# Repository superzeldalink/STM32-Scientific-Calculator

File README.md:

# STM32 Scientific Calculator

## Features
- [x] Basic calculation with
  - [x] $+$, $-$, $\times$, $\div$
  - [x] $\sqrt x$, $\sqrt[a]x$, $a^b$
  - [x] $\sin x$, $\cos x$, $\tan x$ 
  - [ ] $\arcsin x$, $\arccos x$, $\arctan x$ 
  - [ ] $\sinh x$, $\cosh x$, $\tanh x$ 
  - [x] $\ln x$, $\log_{10}x$, $\log_a x$
  - [x] Factorial $!$
- [x] Limits
- [x] Differentiation
- [x] Integration
- [x] Solve equation
- [x] CALC and STO (3 variables for now)
- [x] Convert decimal places into fractions
- [x] Accuracy upto 10 decimal places
- [x] Cursor to move left and right
- [x] Graph function

## Documents
- Schematic: [pcb_schematic.pdf](Report/PCB/pcb_schematic.pdf)
- PCB: [pcb.pdf](Report/PCB/pcb.pdf)
- Project Report: [Report.pdf](Report.pdf)

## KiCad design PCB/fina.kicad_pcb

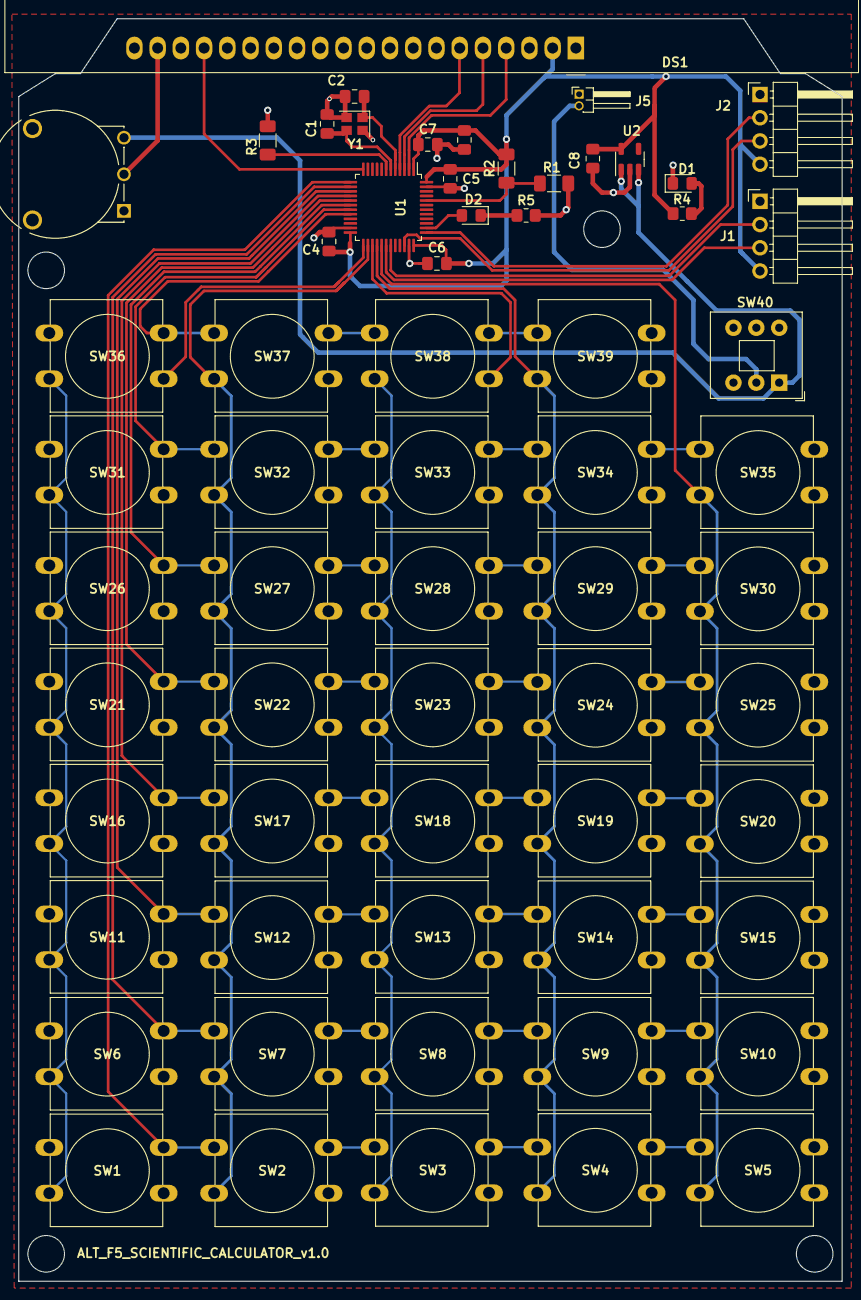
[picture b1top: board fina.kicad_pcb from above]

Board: 2 copper layers, 90.0 x 138.0 mm, 63 parts (0 on the bottom side), 33 nets.

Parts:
C1, C2: 20pF; C_0805_2012Metric_Pad1.18x1.45mm_HandSolder
C3: 4uF; C_0805_2012Metric_Pad1.18x1.45mm_HandSolder
C4, C5, C6, C7: 100pF; C_0805_2012Metric_Pad1.18x1.45mm_HandSolder
C8: 1uF; C_0805_2012Metric_Pad1.18x1.45mm_HandSolder
D1: PWR_LED; LED_0805_2012Metric_Pad1.15x1.40mm_HandSolder
D2: STATUS_LED; LED_0805_2012Metric_Pad1.15x1.40mm_HandSolder
DS1: ST7920; ST7920_128x64
J1: UART; PinHeader_1x04_P2.54mm_Horizontal
J2: SWD; PinHeader_1x04_P2.54mm_Horizontal
J5: PWR; PinHeader_1x02_P1.27mm_Horizontal
R1: 10K; R_1206_3216Metric_Pad1.30x1.75mm_HandSolder
R2, R3: 0; R_1206_3216Metric_Pad1.30x1.75mm_HandSolder
R4, R5: 330; R_0805_2012Metric_Pad1.20x1.40mm_HandSolder
R6: RV100F-30-4K1B-B10K-B301; TRIM_RV100F-30-4K1B-B10K-B301
SW1, SW2, SW3, SW4, SW5, SW6, SW7, SW8, SW9, SW10, SW11, SW12, SW13, SW14, SW15, SW16, SW17, SW18, SW19, SW20, SW21, SW22, SW23, SW24, SW25, SW26, SW27, SW28, SW29, SW30, SW31, SW32, SW33, SW34, SW35, SW36, SW37, SW38, SW39: SW_Push; SW_PUSH-12mm
SW40: SW_SPDT; SW_Push_2P2T_Toggle_CK_PVA2OAH5xxxxxxV2
U1: STM32F302CCTx; LQFP-48_7x7mm_P0.5mm
U2: SPX3819M5-L-3-3; SOT-23-5
Y1: 32MHz; Crystal_SMD_2520-4Pin_2.5x2.0mm

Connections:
3.3V: C3.1, C4.1, C5.1, C6.1, C7.1, C8.1, DS1.2 (VCC), J1.4, J2.4, R2.1, R4.1, U1.1 (VBAT), U1.24 (VDD), U1.36 (VDD), U1.48 (VDD), U2.5 (OUT)
4.2V: R6.3, SW40.1 (A), U2.1 (IN), U2.3 (EN)
/BATT: J5.2, SW40.2 (B)
E: DS1.6 (E), U1.4 (PC15)
GND: C1.2, C2.2, C3.2, C4.2, C5.2, C6.2, C7.2, C8.2, D1.1 (K), DS1.1 (GND), DS1.15 (PSB), DS1.20 (BLK), J1.1, J2.1, J5.1, R1.2, R3.1, R5.2, R6.1, U1.23 (VSS), U1.35 (VSS), U1.47 (VSS), U2.2 (GND), Y1.2, Y1.4
unnamed: D1.2 (A), R4.2
unnamed: D2.2 (A), U1.38 (PA15)
unnamed: D2.1 (K), R5.1
unnamed: DS1.19 (BLA), R6.2
unnamed: J1.2, U1.31 (PA10)
unnamed: J1.3, U1.30 (PA9)
unnamed: J2.2, U1.37 (PA14)
unnamed: J2.3, U1.34 (PA13)
unnamed: R1.1, R2.2, U1.44 (BOOT0)
unnamed: R3.2, U1.7 (NRST)
unnamed: C2.1, U1.5 (PF0), Y1.1
unnamed: C1.1, U1.6 (PF1), Y1.3
RS: DS1.4 (RS), U1.2 (PC13)
RST: DS1.17 (RST), U1.12 (PA2)
RW: DS1.5 (R/W), U1.3 (PC14)
col0: SW1.2, SW6.2, SW11.2, SW16.2, SW21.2, SW26.2, SW31.2, SW36.2, U1.25 (PB12)
col1: SW2.2, SW7.2, SW12.2, SW17.2, SW22.2, SW27.2, SW32.2, SW37.2, U1.26 (PB13)
col2: SW3.2, SW8.2, SW13.2, SW18.2, SW23.2, SW28.2, SW33.2, SW38.2, U1.27 (PB14)
col3: SW4.2, SW9.2, SW14.2, SW19.2, SW24.2, SW29.2, SW34.2, SW39.2, U1.28 (PB15)
col4: SW5.2, SW10.2, SW15.2, SW20.2, SW25.2, SW30.2, SW35.2, U1.29 (PA8)
row0: SW1.1, SW2.1, SW3.1, SW4.1, SW5.1, U1.13 (PA3)
row1: SW6.1, SW7.1, SW8.1, SW9.1, SW10.1, U1.14 (PA4)
row2: SW11.1, SW12.1, SW13.1, SW14.1, SW15.1, U1.15 (PA5)
row3: SW16.1, SW17.1, SW18.1, SW19.1, SW20.1, U1.16 (PA6)
row4: SW21.1, SW22.1, SW23.1, SW24.1, SW25.1, U1.17 (PA7)
row5: SW26.1, SW27.1, SW28.1, SW29.1, SW30.1, U1.18 (PB0)
row6: SW31.1, SW32.1, SW33.1, SW34.1, SW35.1, U1.19 (PB1)
row7: SW36.1, SW37.1, SW38.1, SW39.1, U1.20 (PB2)

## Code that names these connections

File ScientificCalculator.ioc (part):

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Mcu.Name=STM32F302C(B-C)Tx
Mcu.Package=LQFP48
Mcu.UserName=STM32F302CCTx
PA10.Mode=Asynchronous
PA10.Signal=USART1_RX
PA13.Signal=SYS_JTMS-SWDIO
PA14.Signal=SYS_JTCK-SWCLK
PA15.GPIOParameters=GPIO_Label
PA15.GPIO_Label=STATUS_LED
PA15.Signal=GPIO_Output
PA2.GPIOParameters=GPIO_Label
PA2.GPIO_Label=LCD_RST
PA2.Signal=GPIO_Output
PA3.GPIOParameters=GPIO_PuPd,GPIO_Label,GPIO_Mode
PA3.GPIO_Label=ROW0
PA3.GPIO_Mode=GPIO_MODE_INPUT
PA3.GPIO_PuPd=GPIO_PULLUP
PA3.Signal=GPIO_Input
PA4.GPIOParameters=GPIO_PuPd,GPIO_Label,GPIO_Mode
PA4.GPIO_Label=ROW1
PA4.GPIO_Mode=GPIO_MODE_INPUT
PA4.GPIO_PuPd=GPIO_PULLUP
PA4.Signal=GPIO_Input
PA5.GPIOParameters=GPIO_PuPd,GPIO_Label,GPIO_Mode
PA5.GPIO_Label=ROW2
PA5.GPIO_Mode=GPIO_MODE_INPUT
PA5.GPIO_PuPd=GPIO_PULLUP
PA5.Signal=GPIO_Input
PA6.GPIOParameters=GPIO_PuPd,GPIO_Label,GPIO_Mode
PA6.GPIO_Label=ROW3
PA6.GPIO_Mode=GPIO_MODE_INPUT
PA6.GPIO_PuPd=GPIO_PULLUP
PA6.Signal=GPIO_Input
PA7.GPIOParameters=GPIO_PuPd,GPIO_Label,GPIO_Mode
PA7.GPIO_Label=ROW4
PA7.GPIO_Mode=GPIO_MODE_INPUT
PA7.GPIO_PuPd=GPIO_PULLUP
PA7.Signal=GPIO_Input
PA8.GPIOParameters=GPIO_Label
PA8.GPIO_Label=COL4
PA8.Signal=GPIO_Output
PA9.Mode=Asynchronous
PA9.Signal=USART1_TX
PB0.GPIOParameters=GPIO_PuPd,GPIO_Label,GPIO_Mode
PB0.GPIO_Label=ROW5
PB0.GPIO_Mode=GPIO_MODE_INPUT
PB0.GPIO_PuPd=GPIO_PULLUP
PB0.Signal=GPIO_Input
PB1.GPIOParameters=GPIO_PuPd,GPIO_Label,GPIO_Mode
PB1.GPIO_Label=ROW6
PB1.GPIO_Mode=GPIO_MODE_INPUT
PB1.GPIO_PuPd=GPIO_PULLUP
PB1.Signal=GPIO_Input
PB12.GPIOParameters=GPIO_Label
PB12.GPIO_Label=COL0
PB12.Signal=GPIO_Output
PB13.GPIOParameters=GPIO_Label
PB13.GPIO_Label=COL1
PB13.Signal=GPIO_Output
PB14.GPIOParameters=GPIO_Label
PB14.GPIO_Label=COL2
PB14.Signal=GPIO_Output
PB15.GPIOParameters=GPIO_Label
PB15.GPIO_Label=COL3
PB15.Signal=GPIO_Output
PB2.GPIOParameters=GPIO_PuPd,GPIO_Label,GPIO_Mode
PB2.GPIO_Label=ROW7
PB2.GPIO_Mode=GPIO_MODE_INPUT
PB2.GPIO_PuPd=GPIO_PULLUP
PB2.Signal=GPIO_Input
PC13.GPIOParameters=GPIO_Label
PC13.GPIO_Label=LCD_RS
PC13.Signal=GPIO_Output
PC14-OSC32_IN.GPIOParameters=GPIO_Label
PC14-OSC32_IN.GPIO_Label=LCD_R
PC14-OSC32_IN.Signal=GPIO_Output
PC15-OSC32_OUT.GPIOParameters=GPIO_Label
PC15-OSC32_OUT.GPIO_Label=LCD_E
PC15-OSC32_OUT.Signal=GPIO_Output
PF0-OSC_IN.Mode=HSE-External-Oscillator
PF0-OSC_IN.Signal=RCC_OSC_IN
PF1-OSC_OUT.Mode=HSE-External-Oscillator
PF1-OSC_OUT.Signal=RCC_OSC_OUT
RCC.HSEPLLFreq_Value=16000000
RCC.HSE_VALUE=32000000
RCC.SYSCLKFreq_VALUE=32000000
RCC.SYSCLKSourceVirtual=RCC_SYSCLKSOURCE_HSE
board=custom

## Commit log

2023-03-12 Update $x$, $y$, $z$ font
2023-03-12 Update x, y, z font
2023-03-12 Add find limit feature. Add pos/neg infty
2023-03-12 Add assign feature. Optimizations
2023-03-14 Add SOLVE feature. Bug fixes
2023-03-19 Fix operators precedence
2023-04-29 update solve
2023-04-29 store result into ANS after solving
2023-04-29 validation for DOTs
2023-04-29 update key debounce
2023-04-30 update cursor
2023-04-30 update key arrangement
2023-05-02 Update Plot Function
2023-05-03 Font update
2023-05-03 Add hold for keys in graph mode
2023-05-03 Update UX, fix div by zero
2023-05-04 Add mode menu
2023-05-06 add cursor for showing coordinates
2023-05-06 Add ABS
2023-05-07 reorder precedences, bug fixes
2023-05-09 Add integral, add loading screen
2023-05-12 Implement on STM32F302CCT6
2023-05-14 Update UART (connect PC to calc faster)
2023-05-22 Add Splash Screen
2023-05-23 convert HAL to registers (GPIO), implement status led
2023-12-17 Upload PCB, Report
